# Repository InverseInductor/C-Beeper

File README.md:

# c-beeper
Curious C-beeper - Kicad design

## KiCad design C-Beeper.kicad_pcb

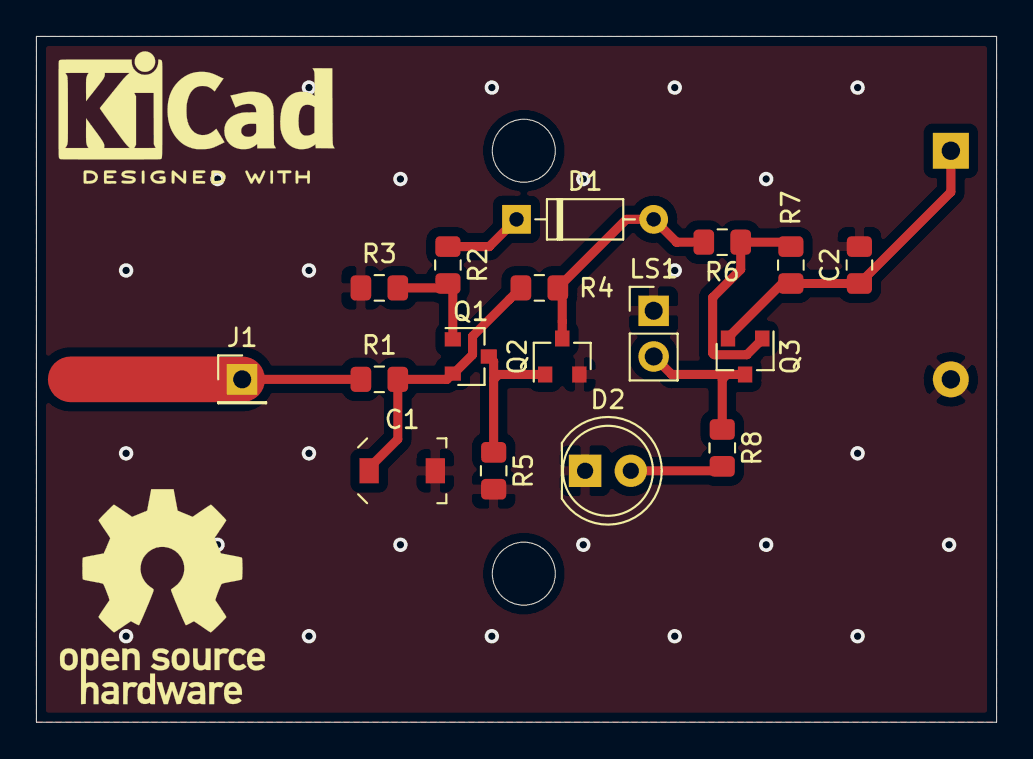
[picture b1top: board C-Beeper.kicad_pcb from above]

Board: 2 copper layers, 53.3 x 38.1 mm, 18 parts (1 on the bottom side), 11 nets.

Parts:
BT1: Battery_Cell; BatteryHolder_Keystone_2479_3xAAA
C1: CTRIM; C_Trimmer_Sprague-Goodman_SGC3
C2: 1nF; C_0805_2012Metric_Pad1.15x1.40mm_HandSolder
D1: 1N4148; D_DO-35_SOD27_P7.62mm_Horizontal
D2: LED; LED_D5.0mm
J1: Conn_01x01_Male; PinHeader_1x01_P2.54mm_Vertical
LS1: Speaker_Crystal; PinHeader_1x02_P2.54mm_Vertical
Q1, Q3: BC859; SOT-23
Q2: BC849; SOT-23
R1: 1M; R_0805_2012Metric_Pad1.15x1.40mm_HandSolder
R2, R4: 2.2M; R_0805_2012Metric_Pad1.15x1.40mm_HandSolder
R3: 5.6M; R_0805_2012Metric_Pad1.15x1.40mm_HandSolder
R5: 1.5M; R_0805_2012Metric_Pad1.15x1.40mm_HandSolder
R6, R7: 33k; R_0805_2012Metric_Pad1.15x1.40mm_HandSolder
R8: 270; R_0805_2012Metric_Pad1.15x1.40mm_HandSolder

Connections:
GND: BT1.2, C1.2, C2.2, D2.1, LS1.1, Q2.2, R3.2, R5.2
unnamed: C1.1, Q1.2, R1.1, R4.2
unnamed: D1.1, R2.1
unnamed: D1.2, Q2.3, R4.1, R6.2
unnamed: D2.2, R8.2
unnamed: J1.1, R1.2
unnamed: LS1.2, Q3.3, R8.1
unnamed: Q1.1, R2.2, R3.1
unnamed: Q1.3, Q2.1, R5.1
unnamed: Q3.1, R6.1, R7.2
VCC: BT1.1, C2.1, Q3.2, R7.1

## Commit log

2019-06-07 Schematic Created
    Initial schematic layout complete. Values added for all components. Will most likely make this version through-hole.
2019-06-07 Annotation and footprints
    Decided to go with SMD. Not a fan of the mix of SMD and through-hole, will need to find replacements for some parts
2019-06-08 PCB layed out.
    Part substitutions for SMD equivalents complete. Only the LED, a diode and the beeper are left as through-hole. Just need to generate the gerbers
2019-06-28 First iteration completed
    PCB layout complete and gerbers generated. A mix of through-hole and SMD was used to match what I have lying around. Long pad on the input is to allow a pogo pin to be soldered on.
